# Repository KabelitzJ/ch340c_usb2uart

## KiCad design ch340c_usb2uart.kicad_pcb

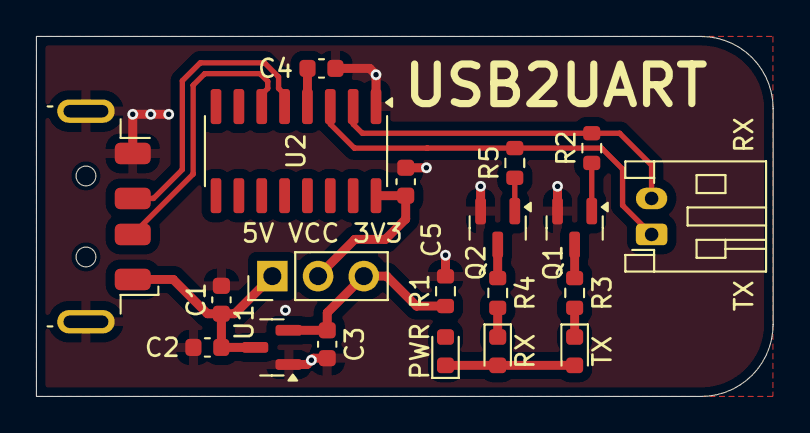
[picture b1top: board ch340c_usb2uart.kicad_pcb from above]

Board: 2 copper layers, 40.9 x 20.0 mm, 20 parts (0 on the bottom side), 9 nets.

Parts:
C1: 4u7; C_0603_1608Metric
C2, C3: 1u; C_0603_1608Metric
C4, C5: 100n; C_0603_1608Metric
J1: USB_A; USB_A_Molex_48037-2200_Horizontal
J2: Conn_01x02_Socket; JST_PH_S2B-PH-K_1x02_P2.00mm_Horizontal
J3: Conn_01x03_Pin; PinHeader_1x03_P2.54mm_Vertical
PWR: PWR; LED_0603_1608Metric
Q1, Q2: BC856; SOT-23
R1, R3, R4: 330; R_0603_1608Metric
R2, R5: 4k7; R_0603_1608Metric
RX: RX (Green); LED_0603_1608Metric
TX: TX (Orange); LED_0603_1608Metric
U1: MCP1700x-330xxTT; SOT-23
U2: CH340C; SOIC-16_3.9x9.9mm_P1.27mm

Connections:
+3V3: C3.1, J3.3, PWR.1 (K), PWR.2 (A), Q1.3 (C), Q2.3 (C), R1.1, R3.1, R3.2, R4.1, R4.2, RX.1 (K), RX.2 (A), TX.1 (K), TX.2 (A), U1.2 (VO)
+5V: C1.1, C2.1, J1.1 (VBUS), J3.1, U1.3 (VI)
GND: C1.2, C2.2, C3.2, C4.2, C5.2, J1.4 (GND), J1.5 (Shield), Q1.2 (E), Q2.2 (E), R1.2, U1.1 (GND), U2.1 (GND)
RX: J2.1, Q2.1 (B), R5.1, R5.2, U2.3 (RXD)
TX: J2.2, Q1.1 (B), R2.1, R2.2, U2.2 (TXD)
USB_D+: J1.3 (D+), U2.5 (UD+)
USB_D-: J1.2 (D-), U2.6 (UD-)
V3: C4.1, U2.4 (V3)
VCC: C5.1, J3.2, U2.16 (VCC)

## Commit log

2025-03-14 sdfsd
